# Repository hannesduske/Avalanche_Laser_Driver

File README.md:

# Nanosecond Avalanche Laser Driver

This avalanche driver generates $\mathbf{2-3\ \mathrm{ns}}$ pulses with peak pulse currents up to $\mathbf{150\ \mathrm{A}}$.
The driver integrates an adjustable boost converter to generate up to $\mathbf{320\ \mathrm{V}}$ from a low-voltage supply.

<div align="center">
<table style="border: none;">
  <tr>
    <td style="text-align:center">
      <br>
    </td>
    <td style="text-align:center">
      <br>
    </td>
  </tr>
</table>
</div>

## ⚠️ Safety Warning

**This project involves high-voltage electronics, high peak currents, and potentially hazardous laser radiation. Anyone building, modifying, or operating this design is responsible for understanding and managing these risks.**

> ⚠️ This repository contains engineering documentation and experimental hardware designs.
> It is not a certified, production-ready, or safety-tested device.

> ⚠️ The circuit contains hazardous high voltages, stored energy, and extremely high peak currents.
> Dangerous voltages may remain present even after the power source has been disconnected.

> ⚠️ Laser diodes driven by this circuit may emit optical pulses capable of causing immediate and permanent eye injury.
> Depending on the laser diode used, hazardous radiation may be invisible.

> ⚠️ Never operate this circuit without appropriate laser safety procedures, protective eyewear suitable for the wavelength used, and adequate electrical safety precautions.

<div align="center">
<table style="border: none;">
  <tr>
    <td style="text-align:center">
      <br>
    </td>
    <td style="text-align:center">
      <br>
    </td>
  </tr>
</table>

**Refer to [this explicit safety statement](SAFETY.md) for more information.**

</div>

## Table of Contents

- [1. Technical Specification](#1-technical-specification)
  - [1.1 Key Features](#11-key-features)
  - [1.2 Design Specification](#12-design-specification)
  - [1.3 Measured Performance](#13-measured-performance)
- [2. Circuit Design](#2-circuit-design)
  - [2.1 Overview](#21-overview)
  - [2.2 Input Protection](#22-input-protection)
  - [2.3 Boost Converter](#23-boost-converter)
  - [2.4 Avalanche Output Stage](#24-avalanche-output-stage)
  - [2.5 Trigger Input Stage](#25-trigger-input-stage)
- [3. PCB Layout](#3-pcb-layout)
  - [3.1 Physical Dimensions](#31-physical-dimensions)
  - [3.2 Peripheral Components](#32-peripheral-components)
  - [3.3 Assembled Driver Boards](#33-assembled-driver-boards)
- [4. Driver Performance](#4-driver-performance)
  - [4.1 Output Voltage](#41-output-voltage)
  - [4.2 Short Circuit Test](#42-short-circuit-test)
  - [4.3 Blue LED Performance](#43-blue-LED-performance)
  - [4.4 PLPT9 450LC_E Performance](#44-plpt9-450lc_e-performance)
- [5. Protective Cover](#5-protective-cover)
- [6. References](#6-references)
  - [6.1 Datasheets of Main Components](#61-datasheets-of-main-components)
  - [6.2 Reference Designs](#62-reference-designs)
  - [6.3 General Resources](#63-general-resources)
  - [6.4 Design Tools](#64-design-tools)

## 1. Technical Specification

### 1.1 Key Features

This driver circuit is built around the [FMMT417](https://www.diodes.com/datasheet/download/FMMT417.pdf) avalanche transistor and is designed to operate up to the transistor's collector-emitter voltage rating of $320\ \mathrm{V}$.
The high voltage is generated by an integrated [LT8365](https://www.analog.com/media/en/technical-documentation/data-sheets/lt8365.pdf) boost converter and can be adjusted from $160\ \mathrm{V}$ to $320\ \mathrm{V}$ to control the output pulse current.

The driver is externally triggered through a transformer-isolated $50\ \Omega$ input.
The trigger signal is internally buffered, significantly improving output pulse consistency across a wide range of trigger amplitudes and waveforms.

For monitoring the generated output pulses, the driver includes a current-sense output with a sensitivity of $100\ \mathrm{A/V}$, enabling direct observation and measurement of the output pulse waveform.

### 1.2 Design Specification

<div align="center">

| Parameter | Value |
|-|-|
| Input Voltage | $9\ \mathrm{V}$ to $30\ \mathrm{V}$ |
| Output Voltage | $160\ \mathrm{V}$ to $320\ \mathrm{V}$ |
| Output Capacitance | $200\ \mathrm{pF}$ | 
| Current Sense Output | $100\ \mathrm{A}/\mathrm{V}$ into a $50\ \Omega$ load|
| Input Protection | Reverse voltage protection <br> Short-circuit protection |
| Trigger Input | $50\ \Omega$ Input <br> Internally buffered <br> Transformer-isolated <br> Immune to DC trigger signals |

</div>

> ℹ️ The upper voltage limit is chosen to match the FMMT417's collector-emitter voltage rating of $320\ \mathrm{V}$.

> ℹ️ The actual cutoff voltage of the driver input is $7.5\ \mathrm{V}$, but it is not guaranteed that the boost converter can reach its maximum output voltage with inputs below $9\ \mathrm{V}$.

### 1.3 Measured Performance

<div align="center">

| Parameter | Value |
|-|-|
| Shortest Pulse Width | $2\ \mathrm{ns}$ |
| Maximum Pulse Current | $150\ \mathrm{A}$ |
| Minimum Avalanche Voltage | $215\ \mathrm{V}$|
| Parasitic Output Inductance | $5.5\ \mathrm{nH}$ |
| Maximum Frequency | $20\ \mathrm{kHz}$ |

</div>

> ℹ️ The maximum frequency can be increased by replacing the $47\ \mathrm{k}\Omega$ charge current-limiting resistor with a smaller one.
Read [this](#42-short-circuit-test) for details.

## 2. Circuit Design

### 2.1 Overview

<div align="center">
  <br>
</div>

The complete schematic is available [here](01_Docs/02_Schematic/avalanche_laser_driver_v0_2.pdf) as PDF.

### 2.2 Input Protection

<div align="center">
  <br>
</div>

The driver is protected against reverse input voltages through MOSFET $\mathrm{Q1}$.
Additionally, the input stage includes an SMD fuse for short-circuit protection.
A switch is added to physically turn the driver on and off.
Two green LEDs indicate whether the DC input is connected correctly and whether the switch is turned on.

### 2.3 Boost Converter

<div align="center">
  <br>
</div>

The high voltage output is generated with an LT8365 boost converter.
Two diode-capacitor stages are added to the output of the boost converter to reach the voltage rating of the FMMT417.
The two additional stages reduce the current available for charging the output capacitors and the output charging resistor $\mathrm{R12}$ is sized accordingly.

The output voltage is set by the feedback network formed by $\mathrm{R5}$, $\mathrm{R7}$ and $\mathrm{RV1}$.
The ratio of $\mathrm{R5}$ to $\mathrm{R7}$ sets the maximum output voltage $\mathrm{HV\_OUT}$ and $\mathrm{R7}$ is tuned to achieve a $320\ \mathrm{V}$ output with the assembled circuit.
The theoretical maximum voltage with the selected values $\mathrm{R5}=1\ \mathrm{M}\Omega$ and $\mathrm{R7}=4.81\ \mathrm{k}\Omega$ is $334\ \mathrm{V}$.

The potentiometer $\mathrm{RV1}$ sets the adjustment range of the output voltage.
It should cover the entire range from the FMMT417's minimum avalanche voltage (around $215\ \mathrm{V}$) to its collector-emitter voltage rating of $320\ \mathrm{V}$.
The chosen value of $5\ \mathrm{k}\Omega$ is larger than necessary for that purpose, as it gives a lower voltage limit of $160\ \mathrm{V}$.
Using a smaller value potentiometer (around $3.3\ \mathrm{k}\Omega$) would enable finer adjustments while still covering the entire voltage range.

The third terminal of $\mathrm{RV1}$ is also connected so that, if the potentiometer wiper fails open-circuit, the potentiometer defaults to its maximum resistance.
In that case the boost converter falls back to its minimum output voltage.

A red LED indicates whether the boost converter output capacitors are charged.

### 2.4 Avalanche Output Stage

<div align="center">
  <br>
</div>

The core of this driver is a basic avalanche transistor circuit.
The high voltage output capacitors $\mathrm{C11}$ and $\mathrm{C12}$ are charged through the current-limiting resistor $\mathrm{R12}$ and the charging diode $\mathrm{D9}$.
Once charged, a small signal at the base of the transistor $\mathrm{Q2}$ initiates avalanche breakdown across the collector-emitter junction, resulting in the rapid discharge of $\mathrm{C11}$ and $\mathrm{C12}$ through the output load.
After an output pulse the capacitors recharge again.

One goal of the output stage is to minimize the parasitic inductance as it is the main limiting factor for the peak pulse current during fast transients.
Therefore, multiple smaller output capacitors in parallel are preferred over a single large one because the effective equivalent series inductance (ESL) is reduced.
In this design two $100\ \mathrm{pF}$ 0603 capacitors are used, as the only other smaller capacitors with sufficient current rating ($47\ \mathrm{pF}$) were not in stock at the time the driver boards were assembled.

The components $\mathrm{C11}$, $\mathrm{C12}$ and $\mathrm{R12}$ form an RC low-pass which sets the maximum frequency at which the circuit can be triggered.
Assuming that approximately three time constants are required for capacitor recharge, the maximum frequency is approximately $f_{max}\approx \frac{1}{3\cdot \mathrm{R_{12}}(\mathrm{C_{11}}+\mathrm{C_{12}})} = \frac{1}{3 \cdot 47\ \mathrm{k}\Omega(100\ \mathrm{pF}+100\ \mathrm{pF})} \approx 35\ \mathrm{kHz}$.
The actual frequency is lower than that because the capacitors do not start charging immediately after a pulse, as is shown by the measurements below.

In this design the driver capacitance is $200\ \mathrm{pF}$ with a maximum output voltage of $320\ \mathrm{V}$.
The maximum stored electrical energy per pulse is $E_p=\frac{1}{2}\cdot C \cdot U^2=\frac{1}{2}\cdot 200\ \mathrm{pF} \cdot (320\ \mathrm{V})^2=10.24\ \mu\mathrm{J}$.
With the maximum achievable trigger frequency of $20\ \mathrm{kHz}$ (see measurements below) the maximum theoretical average output power is approximately $P=E_p\cdot f=10.24\ \mu\mathrm{J}\cdot 20\ \mathrm{kHz}=205\ \mathrm{mW}$

The $20\ \mathrm{m}\Omega$ four-terminal shunt resistor $\mathrm{R19}$ is placed in series with the driver output, enabling the pulse current to be monitored.
This low-value resistor has a minimal effect on the pulse current while providing accurate measurements through its two sense terminals.
The circuit's sense output is designed to drive a $50\ \Omega$-terminated oscilloscope input.
Together with the external $50\ \Omega$ termination resistor, the internal $50\ \Omega$ resistor $\mathrm{R15}$ forms a $1:2$ voltage divider.
The $20\ \mathrm{m}\Omega$ shunt resistor provides a sensitivity of $20\ \mathrm{mV/A}$.
This is halved by the voltage divider, resulting in a final sensitivity of $10\ \mathrm{mV/A}$ or $100\ \mathrm{A/V}$ at the circuit's current sense output.

### 2.5 Trigger Input Stage

<div align="center">
  <br>
</div>

The trigger input feeds a $50\ \Omega$ terminated balun transformer $\mathrm{TR1}$ for isolation and for high-pass filtering of the input.
The transformed signal is then buffered by the high-speed BJT $\mathrm{Q3}$ which is connected to the FMMT417's base through the current-limiting resistor $\mathrm{R14}$.
The pull-down resistor $\mathrm{R21}$ helps turn off $\mathrm{Q2}$ rapidly after an avalanche and prevents accidental triggering caused by a floating base.

The high-pass property of the balun transformer also prevents damage to $\mathrm{Q2}$ from DC input signals which would otherwise keep the avalanche transistor turned on.

## 3. PCB Layout

### 3.1 Physical Dimensions

Below is an illustration of the physical outline and hole spacing of the PCB V0.2.
The mounting holes fit the standard $25\ \mathrm{mm}$ hole pattern of optical benches.

<div align="center">
  <br>
</div>

### 3.2 Peripheral Components

Below is a functional description of the main peripheral components of the PCB.

<div align="center">
<br>

| Reference | Description |
|-|-|
| SW1   | On/off switch. Switches the supply rail of the boost converter. |
| POT1  | Output voltage adjustment. |
| LED1  | Indicates DC input is connected. |
| LED2  | Indicates the boost converter is supplied. Lights up when SW1 is on. |
| LED3  | Indicates the boost converter output caps are charged. | 
| SMA1  | Trigger input ($50\ \Omega$). | 
| SMA2  | Current sense output ($50\ \Omega$). |
| CONN1 | DC input. 5.5 x 2.1 mm barrel jack (center positive). |
| CONN2 | Driver output. Solder pads ($2\ \mathrm{mm}$ pitch). |
| FUSE1 | 0603 SMD Fuse ($3\ \mathrm{A}$) for short-circuit protection. |
</div>

### 3.3 Assembled Driver Boards

The two driver boards shown below were assembled for a performance test.
The left driver was assembled with an ams OSRAM PLPT9 450LC_E laser diode and the right one with a blue LED.

<div align="center">
<table style="border: none;">
  <tr>
    <td style="text-align:center">
      <br>
      <p>Top view of the V0.2 PCBs</p>
    </td>
    <td style="text-align:center">
        <br>
      <p>Front view of the V0.2 PCBs</p>
    </td>
  </tr>
</table>
</div>

## 4. Driver Performance

Driver performance was evaluated using the following configurations:
- Output pads shorted with solder bridge
- Blue LED (right PCB in above pictures)
- ams OSRAM PLPT9 450LC_E (left PCB in above pictures)

### 4.1 Output Voltage

The output voltage of the driver is adjustable between $160\ \mathrm{V}$ and $320\ \mathrm{V}$.

<div align="center">
<table style="border: none;">
  <tr>
    <td style="text-align:center">
      <br>
      <p>Lower voltage limit of the boost converter</p>
    </td>
    <td style="text-align:center">
        <br>
      <p>Upper voltage limit of the boost converter</p>
    </td>
  </tr>
</table>
</div>

> ⚠️ The feedback resistors should not be replaced to increase the upper voltage limit above $320\ \mathrm{V}$.
> Increasing the output voltage risks instant destruction of the FMMT417.

### 4.2 Short-Circuit Test

In the first test the output pads of the driver are shorted with a solder bridge.
The output is set to $320\ \mathrm{V}$ and the trigger signal is a $2\ \mathrm{Vpp}$ square wave.

<div align="center">
  <br>
  <p>Short-circuit test at 320 V with a 2 Vpp trigger signal</p>
</div>

The short-circuit test shows that the output oscillates with no load connected.
This is the expected behavior, because the stored energy is dissipated only slowly through the parasitic impedance of the circuit and there is no diode that blocks reverse current.

In the short-circuit test we measured a maximum current of $153\ \mathrm{A}$ with a pulse width of $2.2\ \mathrm{ns}$.

The minimum operating voltage at which avalanche triggering occurs was measured to be 215 V with a 5 V square wave trigger signal.
Note that the minimum voltage depends on the trigger signal amplitude.
The lower the output voltage, the larger the trigger signal amplitude must be to start an avalanche.

We can also approximate the effective parasitic loop inductance of the output stage from the observed oscillation.
For this, we assume an LC oscillator with a frequency of $f = \frac{1}{2 \pi \sqrt{LC}}$.
From the measured oscillation frequency we get $f = 152\ \mathrm{MHz}$ and the output capacitance is $200\ \mathrm{pF}$.
With these values we calculate an inductance of $L = \frac{1}{C(2\pi f)^2} = \frac{1}{200\ \mathrm{pF}(2\pi \cdot 152\ \mathrm{MHz})^2} = 5.46\ \mathrm{nH}$.

<div align="center">
  <br>
  <p>Measurement of the output capacitor charge time</p>
</div>

In a second measurement the maximum trigger frequency is tested.
The measurement shows that the output capacitors start charging only after a delay of $14\ \mathrm{\mu s}$.
This reduces the actual achievable output frequency from the theoretical $35\ \mathrm{kHz}$ to a practically achievable frequency of $20\ \mathrm{kHz}$.

### 4.3 Blue LED Performance

In the second test the output drives a blue LED.
The output is set to $320\ \mathrm{V}$ and the trigger signal is a $2\ \mathrm{Vpp}$ square wave.

<div align="center">
  <br>
  <p>Test with blue LED at 320 V with a 2 Vpp trigger signal</p>
</div>

With the blue LED, the output pulse is significantly different compared to the short-circuit test.
There is a large, narrow current pulse across the diode, followed by a smaller, wider pulse in the reverse direction.
With the blue LED, the maximum current is $70\ \mathrm{A}$ with a $2\ \mathrm{ns}$ pulse width.

In a second test, the optical pulse shape was measured at a lower drive current with the [Fast SiPM Photodetector](https://github.com/hannesduske/Fast_SiPM_Photodetector).
The cyan trace shows the drive-current pulse, and the yellow trace shows the measured SiPM response to the LED's light emission.
The oscilloscope measured pulse widths of $2.35\ \mathrm{ns}$ for the drive-current pulse and $5.55\ \mathrm{ns}$ for the SiPM output.
The SiPM output pulse is significantly wider than the drive-current pulse.

<div align="center">
  <br>
  <p>Drive-current pulse (cyan) through the blue LED and the measured SiPM output (yellow) averaged over 64 measurements.</p>
</div>

### 4.4 PLPT9 450LC_E Performance

In the third test the output drives an ams OSRAM PLPT9 450LC_E.
The output is set to $320\ \mathrm{V}$ and the trigger signal is a $2\ \mathrm{Vpp}$ square wave.

<div align="center">
  <br>
  <p>Test with PLPT9 450LC_E at 320 V with a 2 Vpp trigger signal</p>
</div>

With the PLPT9 laser diode the maximum current is $141\ \mathrm{A}$ with a $2\ \mathrm{ns}$ pulse width.

Note that the oscillation is less damped than with the blue LED and more similar to the short-circuit test.
Presumably this is because of the integrated reverse-protection Zener diode in the PLPT9 package, which protects the sensitive main laser diode against reverse currents.

The optical pulse shape was measured with the [Fast SiPM Photodetector](https://github.com/hannesduske/Fast_SiPM_Photodetector).
The oscillations in the drive-current pulse are also visible as additional peaks in the measured SiPM response, showing that they carry through to the laser's light emission.
Similar to the short-circuit test, the oscillation frequency is approximately 150 MHz.

<div align="center">
  <br>
  <p>Drive-current pulse (cyan) through the PLPT9 450LC_E laser diode and the measured SiPM output (yellow) averaged over 64 measurements.</p>
</div>

## 5. Protective Cover

A 3D printed cover has been designed for the driver.
It covers the high voltage components and exposes only the peripherals.

The cover is available in two variants.
A monolithic version that is easy to print and a version with **T**rigger/ **S**ense markings for printers with filament change capability.

<div align="center">
<table style="border: none;">
  <tr>
    <td style="text-align:center">
      <br>
      <p>Monolithic cover</p>
    </td>
    <td style="text-align:center">
      <br>
      <p>Cover with Trigger/ Sense markings</p>
    </td>
  </tr>
</table>
</div>

## 6. References
### 6.1 Datasheets of Main Components
- [LT8365](https://www.analog.com/media/en/technical-documentation/data-sheets/lt8365.pdf) Boost converter
- [FMMT417](https://www.diodes.com/datasheet/download/FMMT417.pdf) Avalanche transistor
- [PLPT9 450LC_E](https://look.ams-osram.com/m/8992eec443b4ce2/original/PLPT9-450LC_E.pdf) ams OSRAM Laser Diode

### 6.2 Reference Designs
- [Les' Lab Laser Driver](https://github.com/leswright1977/avalanche-laser-diode-driver) + [Video](https://www.youtube.com/watch?v=3-htF8Jrixo&t=24s) (ZTX415/ 2N5192G)
- [BigPulse Driver](https://github.com/MazinLab/BigPulse) + [Video](https://www.youtube.com/watch?v=OXhiX0EW5MI) (FMMT415TD + LT8365)

### 6.3 General Resources
- Lasercomponents [Whitepaper](https://www.lasercomponents.com/uk/photonics-portal/knowledge-center/whitepapers/drive-electronics-for-pulsed-laser-diodes/)
- Zetex ZTX415 [Application Note AN8](https://user-web.icecube.wisc.edu/~kitamura/NK/Flasher_Board/Useful/research/AN8.pdf)
- Jim Williams Pulser [AN47 Appendix D (p. 93)](https://www.analog.com/media/en/technical-documentation/application-notes/an47fa.pdf)
- Selection and usage of laser safety goggles [DGUV 203-042](https://publikationen.dguv.de/widgets/pdf/download/article/249) (German)
- Continuous wave laser diodes enable fast optoacoustic imaging [ResearchGate](https://www.researchgate.net/publication/321863583_Continuous_wave_laser_diodes_enable_fast_optoacoustic_imaging)

### 6.4 Design Tools
- [LTSpice](https://www.analog.com/en/resources/design-tools-and-calculators/ltspice-simulator.html) Circuit simulation
- [KiCad 10](https://www.kicad.org/blog/2026/03/Version-10.0.0-Released/) Circuit board design
- [SMath Studio](https://smath.com/) Design calculations

## License

This project is licensed under the CERN Open Hardware Licence Version 2 - Permissive ([CERN-OHL-P](https://ohwr.org/cern_ohl_p_v2.txt)).

Third-party datasheets, logos, warning symbols, and referenced documentation remain the property of their respective owners.

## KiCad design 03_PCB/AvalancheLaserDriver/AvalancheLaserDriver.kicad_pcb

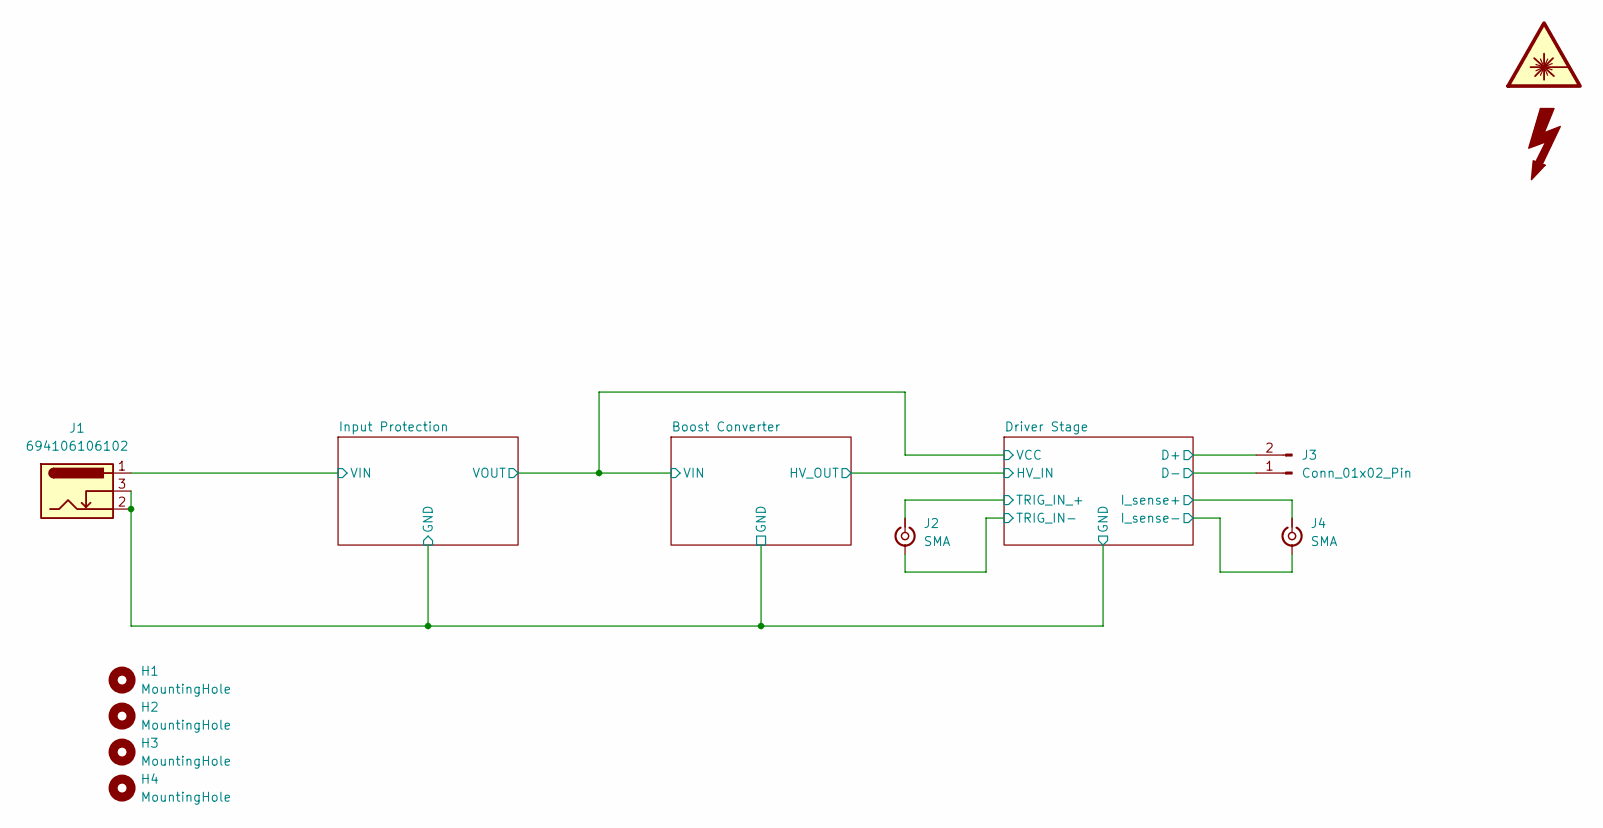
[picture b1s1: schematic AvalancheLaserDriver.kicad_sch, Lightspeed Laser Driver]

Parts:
H1, H2, H3, H4: MountingHole; MountingHole_3.2mm_M3
J1: 694106106102; BarrelJack_Wuerth_694106106102_2.0x5.5mm
J2, J4: SMA; SMA_Wurth_60312002114503_Vertical
J3: Conn_01x02_Pin; R_0815_2038Metric_Pad1.20x4.05mm_HandSolder

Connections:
/Driver Stage/D+: J3.2; also elsewhere on the board
/Driver Stage/D-: J3.1; also elsewhere on the board
/Driver Stage/I_sense+: J4.1 (In); also elsewhere on the board
/Driver Stage/I_sense-: J4.2 (Ext); also elsewhere on the board
/Driver Stage/TRIG_IN-: J2.2 (Ext); also elsewhere on the board
/Driver Stage/TRIG_IN_+: J2.1 (In); also elsewhere on the board
/Input Protection/VIN: J1.1; also elsewhere on the board
GND: J1.2, J1.3; also elsewhere on the board

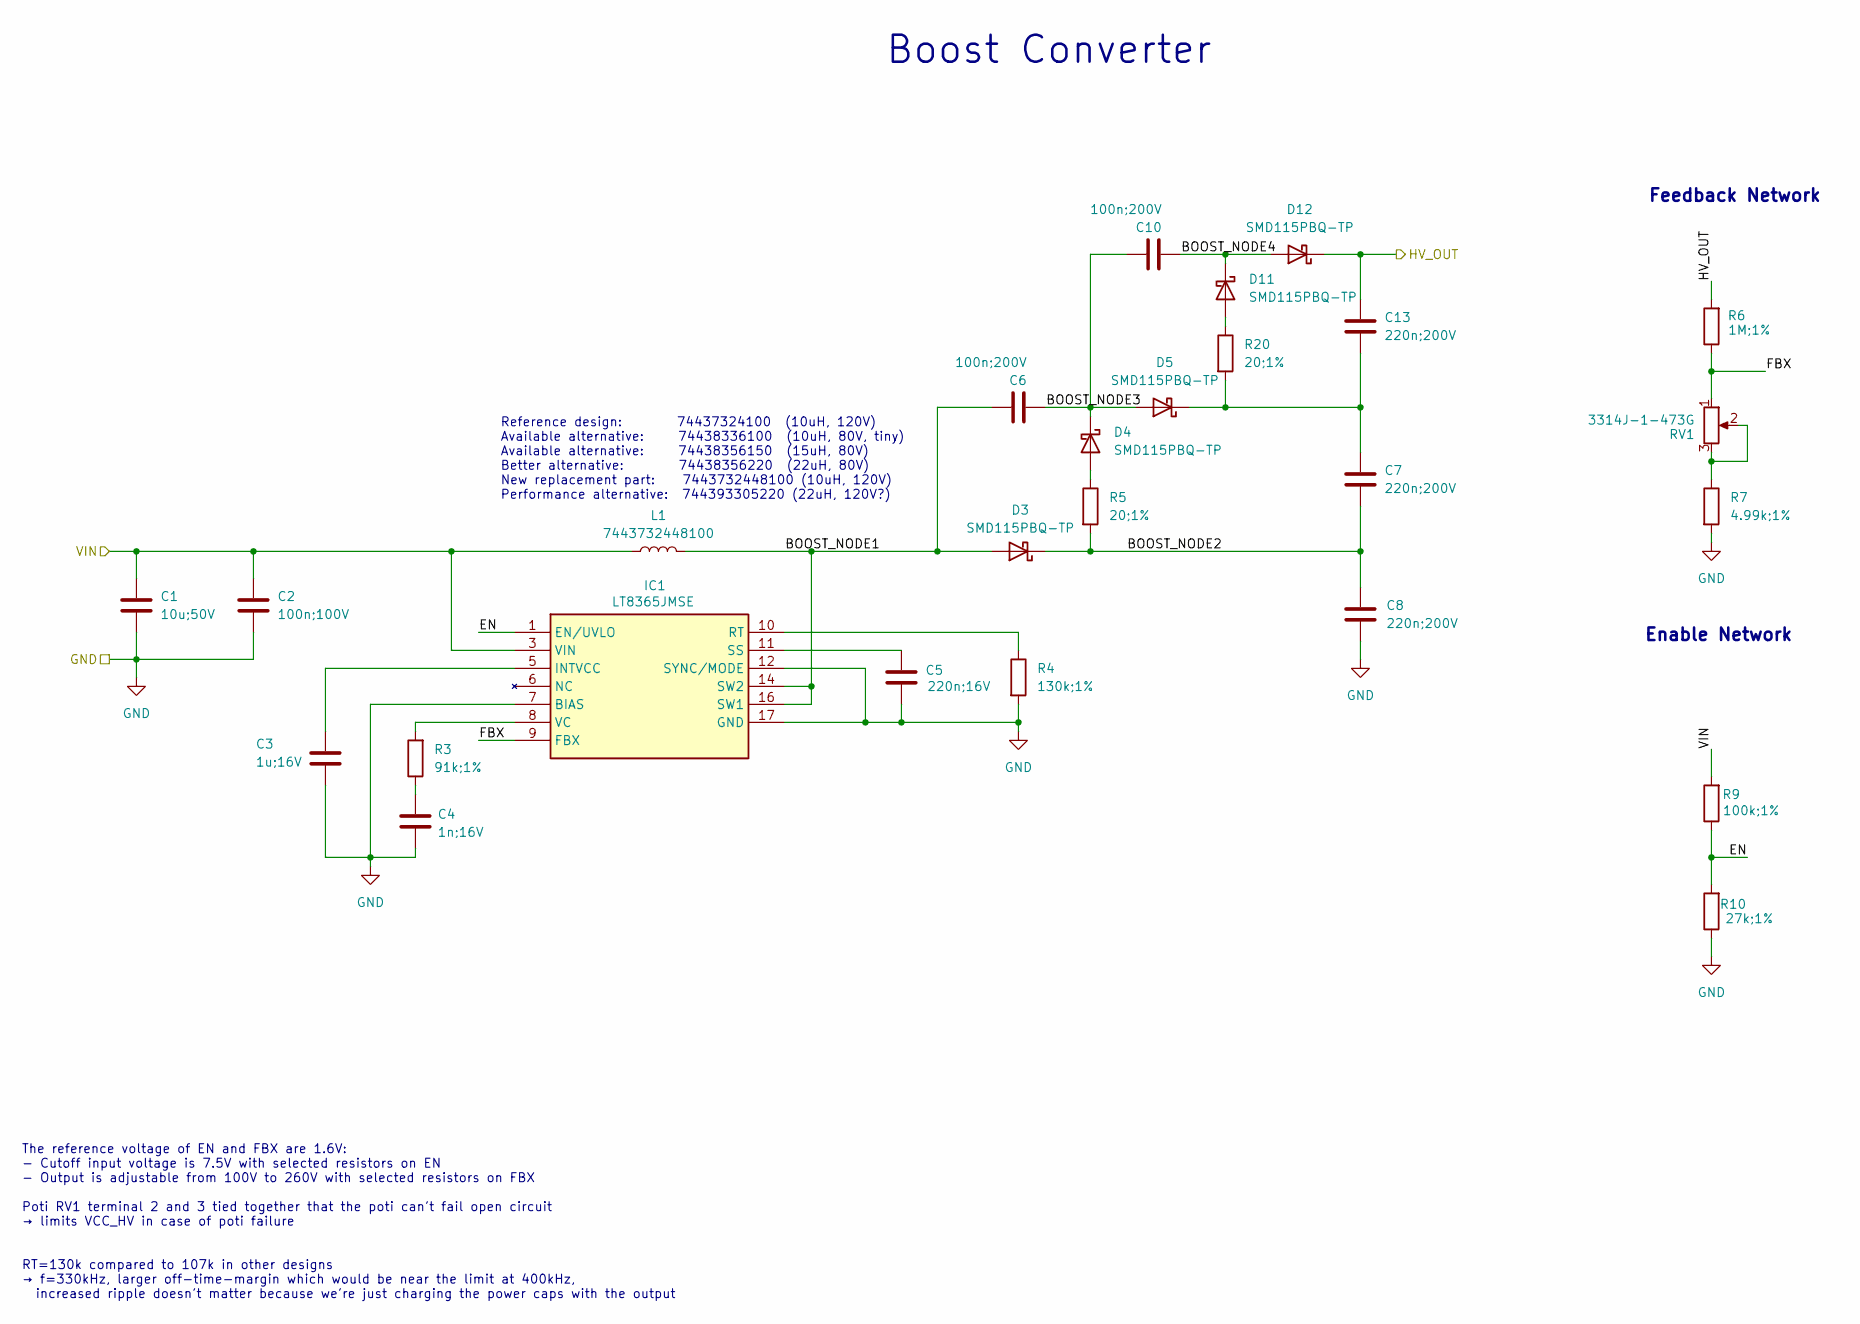
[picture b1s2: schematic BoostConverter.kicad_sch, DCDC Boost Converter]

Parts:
C1: 10u;50V; C_1206_3216Metric
C2: 100n;100V; C_0603_1608Metric
C3: 1u;16V; C_0603_1608Metric
C4: 1n;16V; C_0603_1608Metric
C5: 220n;16V; C_0603_1608Metric
C6, C10: 100n;200V; C_0805_2012Metric
C7, C8, C13: 220n;200V; C_1206_3216Metric
D3, D4, D5, D11, D12: SMD115PBQ-TP; D_SOD-323HE
IC1: LT8365JMSE; Analog_MSOP-12-16-1EP_3x4.039mm_P0.5mm_EP1.651x2.845mm; Mouser Part Number 584-LT8365JMSE
L1: 7443732448100; L_Wurth_WE-LQSH-4020
R3: 91k;1%; R_0603_1608Metric
R4: 130k;1%; R_0603_1608Metric
R5, R20: 20;1%; R_0603_1608Metric
R6: 1M;1%; R_0603_1608Metric
R7: 4.99k;1%; R_0603_1608Metric
R9: 100k;1%; R_0603_1608Metric
R10: 27k;1%; R_0603_1608Metric
RV1: 3314J-1-473G; Potentiometer_Bourns_3314J_Vertical

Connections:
/Boost Converter/BOOST_NODE1: C6.1, D3.2 (A), IC1.14 (SW2), IC1.16 (SW1), L1.2
/Boost Converter/BOOST_NODE2: C7.1, C8.2, D3.1 (K), R5.2
/Boost Converter/BOOST_NODE3: C6.2, C10.1, D4.1 (K), D5.2 (A)
/Boost Converter/BOOST_NODE4: C10.2, D11.1 (K), D12.2 (A)
/Boost Converter/EN: IC1.1 (EN/UVLO), R9.1, R10.2
/Boost Converter/FBX: IC1.9 (FBX), R6.1, RV1.1
/Boost Converter/HV_OUT: C13.2, D12.1 (K), R6.2; also elsewhere on the board
/Boost Converter/VIN: C1.2, C2.2, IC1.3 (VIN), L1.1, R9.2; also elsewhere on the board
GND: C1.1, C2.1, C3.1, C4.1, C5.1, C8.1, IC1.7 (BIAS), IC1.12 (SYNC/MODE), IC1.17 (GND), R4.2, R7.2, R10.1; also elsewhere on the board
unnamed: C4.2, R3.1
unnamed: D4.2 (A), R5.1
unnamed: C7.2, C13.1, D5.1 (K), R20.2
unnamed: D11.2 (A), R20.1
unnamed: C3.2, IC1.5 (INTVCC)
unnamed: IC1.10 (RT), R4.1
unnamed: C5.2, IC1.11 (SS)
unnamed: IC1.8 (VC), R3.2
unnamed: R7.1, RV1.2, RV1.3

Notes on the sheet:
Enable Network
The reference voltage of EN and FBX are 1.6V: - Cutoff input voltage is 7.5V with selected resistors on EN - Output is adjustable from 100V to 260V with selected resistors on FBX Poti RV1 terminal 2 and 3 tied together that the poti can't fail open circuit → limits VCC_HV in case of poti failure RT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
Reference design: 74437324100 (10uH, 120V) Available alternative: 74438336100 (10uH, 80V, tiny) Available alternative: 74438356150 (15uH, 80V) Better alternative: 74438356220 (22uH, 80V) New replacement part: 7443732448100 (10uH, 120V) Performance alternative: 744393305220 (22uH, 120V?)
Boost Converter
Feedback Network

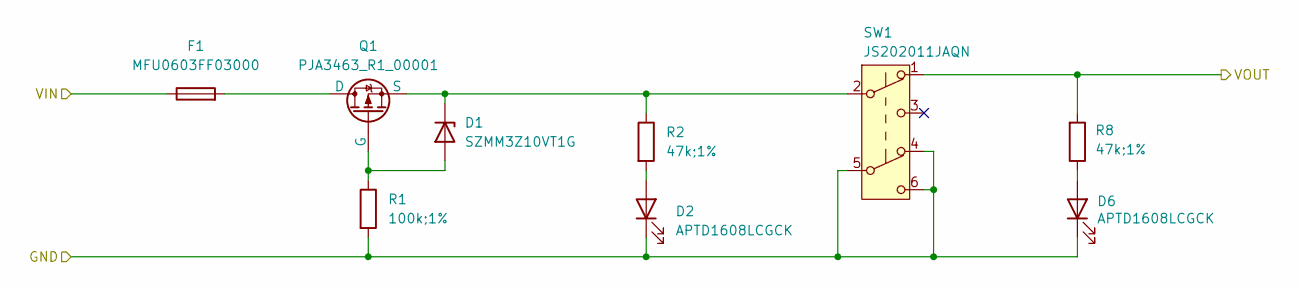
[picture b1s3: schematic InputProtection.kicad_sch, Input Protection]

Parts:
D1: SZMM3Z10VT1G; D_SOD-323
D2, D6: APTD1608LCGCK; LED_0603_1608Metric
F1: MFU0603FF03000; Fuse_0603_1608Metric
Q1: PJA3463_R1_00001; SOT-23
R1: 100k;1%; R_0603_1608Metric
R2, R8: 47k;1%; R_0603_1608Metric
SW1: JS202011JAQN; SW_DPDT_CK_JS202011JCQN

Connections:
/Boost Converter/VIN: R8.2, SW1.1 (A); also elsewhere on the board
/Input Protection/VIN: F1.1; also elsewhere on the board
GND: D2.1 (K), D6.1 (K), R1.2, SW1.4 (A), SW1.5 (B), SW1.6 (C); also elsewhere on the board
unnamed: D1.2 (A), Q1.1 (G), R1.1
unnamed: D1.1 (K), Q1.2 (S), R2.1, SW1.2 (B)
unnamed: D2.2 (A), R2.2
unnamed: D6.2 (A), R8.1
unnamed: F1.2, Q1.3 (D)

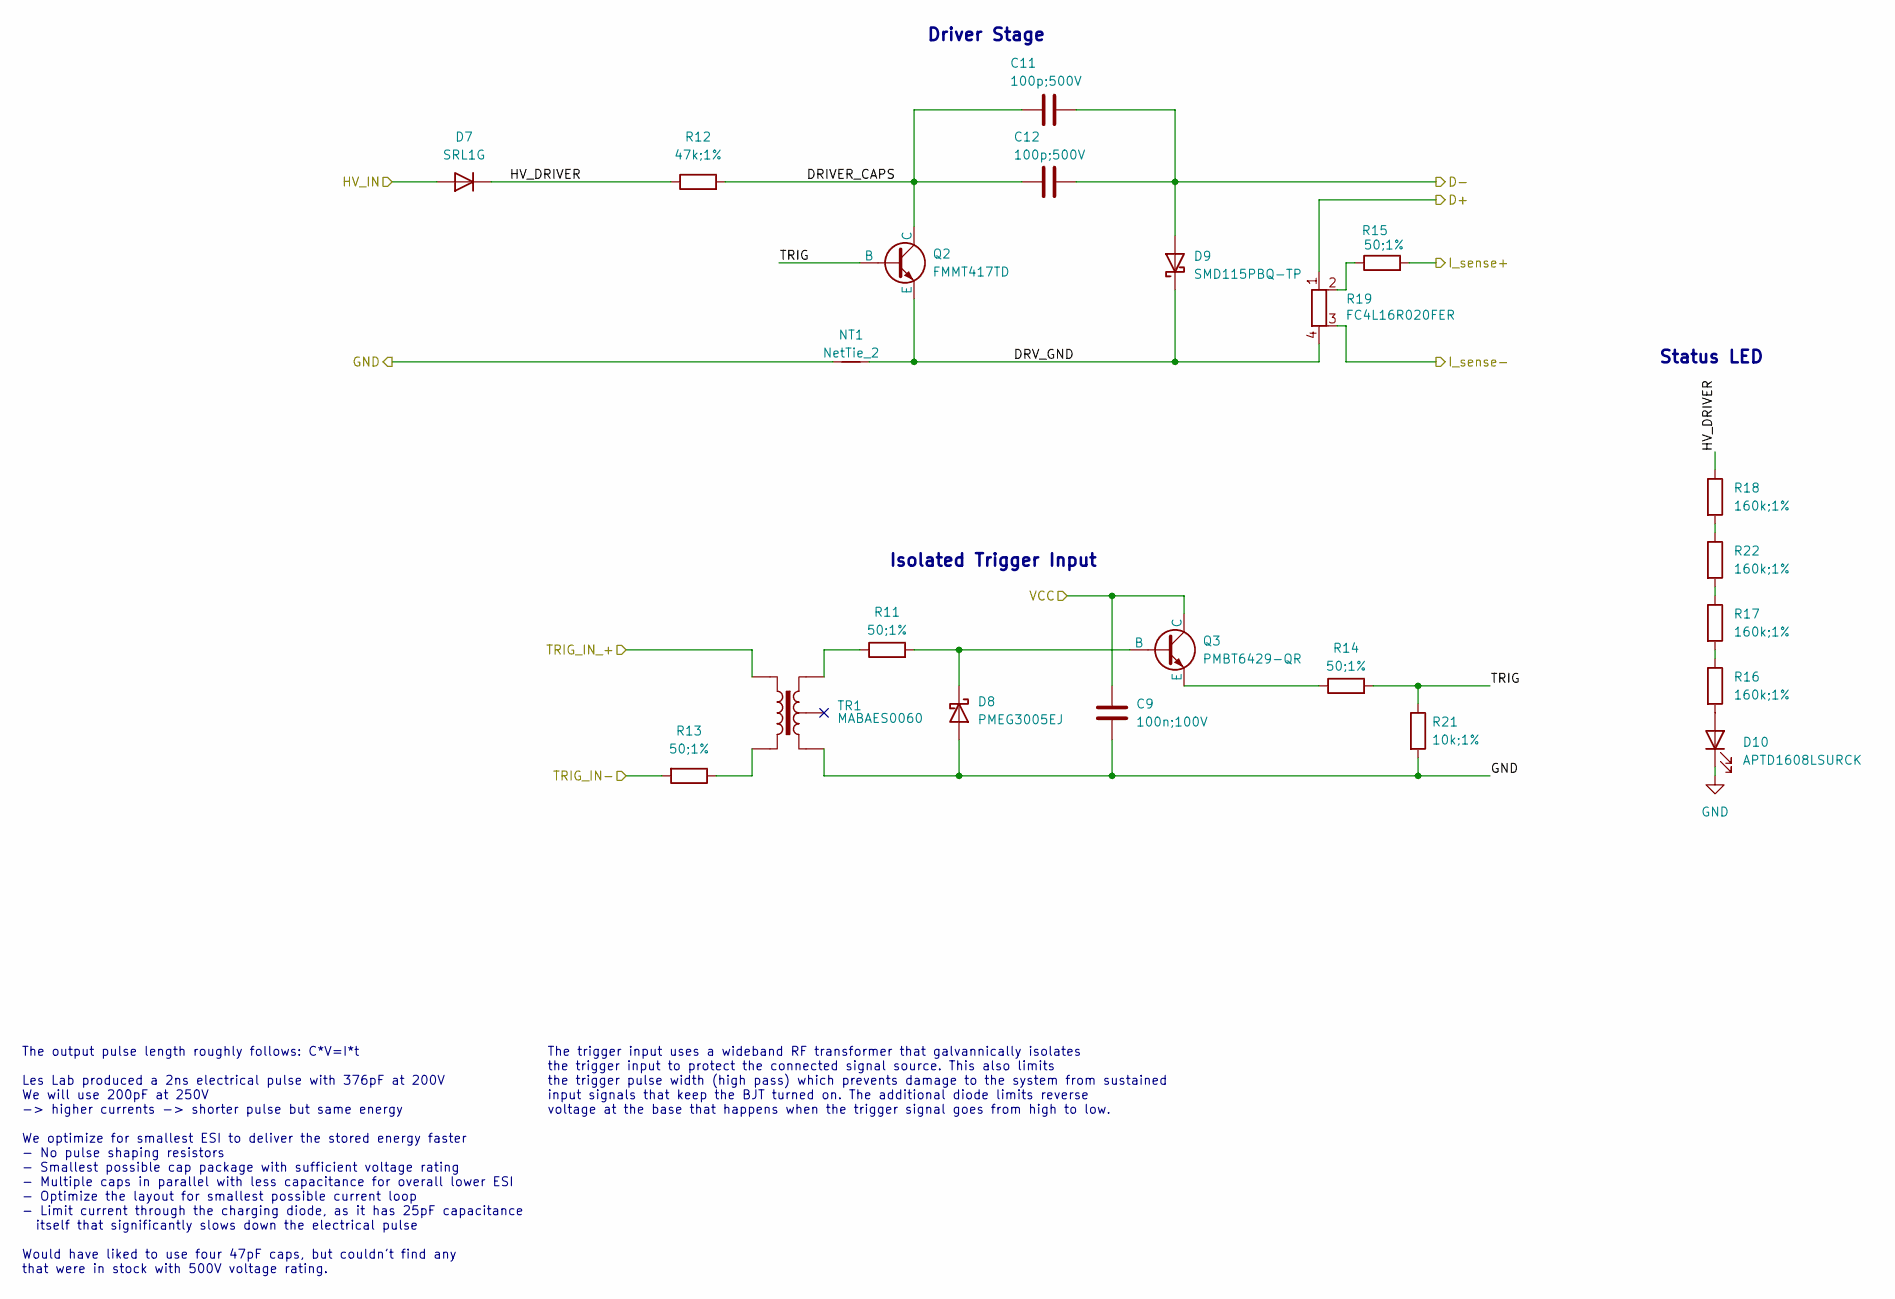
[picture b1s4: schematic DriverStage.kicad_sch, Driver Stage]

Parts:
C9: 100n;100V; C_0603_1608Metric
C11, C12: 100p;500V; C_0603_1608Metric
D7: SRL1G; D_SOD-323HE
D8: PMEG3005EJ; D_SOD-323
D9: SMD115PBQ-TP; D_SOD-323HE
D10: APTD1608LSURCK; LED_0603_1608Metric
NT1: NetTie_2; NetTie-2_THT_Pad0.3mm
Q2: FMMT417TD; TSOT-23
Q3: PMBT6429-QR; TSOT-23
R11, R13, R14, R15: 50;1%; R_0603_1608Metric
R12: 47k;1%; R_0603_1608Metric
R16, R17, R18, R22: 160k;1%; R_0603_1608Metric
R19: FC4L16R020FER; FC4L16
R21: 10k;1%; R_0603_1608Metric
TR1: MABAES0060; Transformer_MACOM_SM-22

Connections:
/Boost Converter/HV_OUT: D7.2 (A); also elsewhere on the board
/Boost Converter/VIN: C9.2, Q3.3 (C); also elsewhere on the board
/Driver Stage/D+: R19.1; also elsewhere on the board
/Driver Stage/D-: C11.2, C12.2, D9.2 (A); also elsewhere on the board
/Driver Stage/DRIVER_CAPS: C11.1, C12.1, Q2.3 (C), R12.2
/Driver Stage/DRV_GND: D9.1 (K), NT1.2, Q2.2 (E), R19.4
/Driver Stage/HV_DRIVER: D7.1 (K), R12.1, R18.1
/Driver Stage/I_sense+: R15.2; also elsewhere on the board
/Driver Stage/I_sense-: R19.3; also elsewhere on the board
/Driver Stage/TRIG: Q2.1 (B), R14.2, R21.1
/Driver Stage/TRIG_IN-: R13.2; also elsewhere on the board
/Driver Stage/TRIG_IN_+: TR1.2; also elsewhere on the board
GND: C9.1, D8.2 (A), D10.1 (K), NT1.1, R21.2, TR1.5; also elsewhere on the board
unnamed: D8.1 (K), Q3.1 (B), R11.2
unnamed: D10.2 (A), R16.2
unnamed: Q3.2 (E), R14.1
unnamed: R11.1, TR1.3
unnamed: R13.1, TR1.1
unnamed: R15.1, R19.2
unnamed: R16.1, R17.2
unnamed: R17.1, R22.2
unnamed: R18.2, R22.1

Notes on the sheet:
The trigger input uses a wideband RF transformer that galvannically isolates the trigger input to protect the connected signal source. This also limits the trigger pulse width (high pass) which prevents damage to the system from sustained input signals that keep the BJT turned on. The additional di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
Isolated Trigger Input
Status LED
The output pulse length roughly follows: C*V=I*t Les Lab produced a 2ns electrical pulse with 376pF at 200V We will use 200pF at 250V -> higher currents -> shorter pulse but same energy We optimize for smallest ESI to deliver the stored energy faster - No pulse shaping resistors - Smallest possible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
Driver Stage

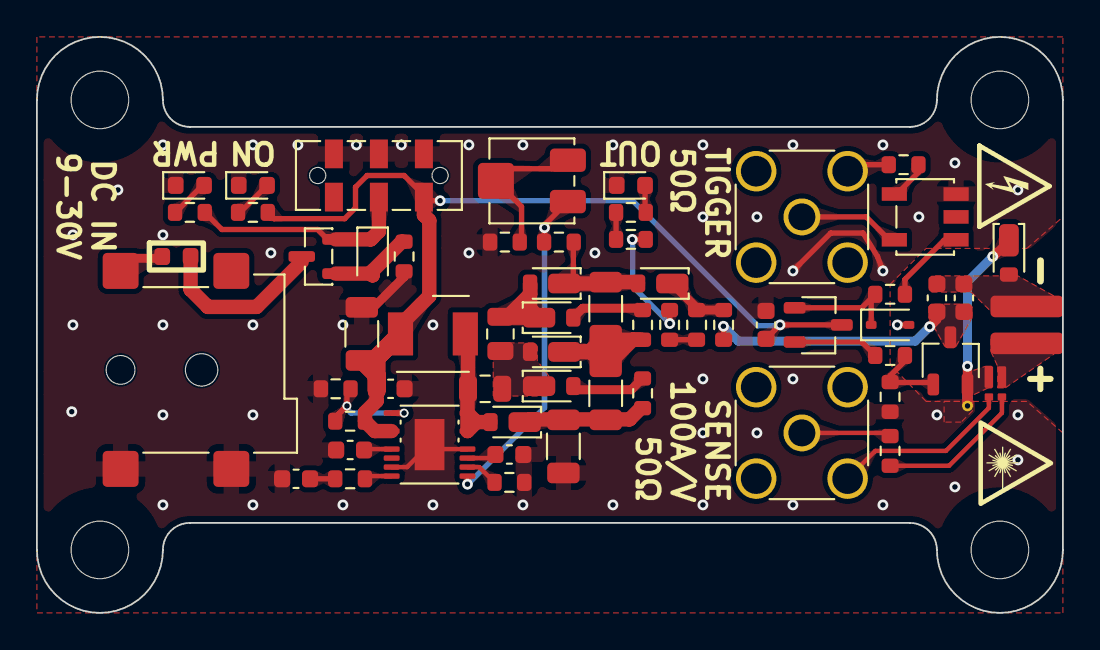
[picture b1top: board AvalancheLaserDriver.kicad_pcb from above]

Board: 2 copper layers, 57.0 x 32.0 mm, 65 parts (0 on the bottom side), 43 nets.

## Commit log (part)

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2026-06-22 feat(pcb): intital pcb layout
2026-06-22 feat(simulation): add a lt8365 simulation including the led driver stage
2026-06-22 feat(pcb): add peripherals to PCB
2026-06-22 feat(pcb): route all traces
2026-06-22 feat(pcb): laser driver layout draft finished, add high voltage indicator LED and discharge path
2026-06-22 feat(pcb): improve the design draft
2026-06-22 feat(pcb): laser driver V0.1 as ordered on 08.03.2026
2026-06-22 chore: restructure desing files in repo
2026-06-22 feat(pcb): add changelog
2026-06-22 refactor(pcb): rename laser driver PCB to AvalancheLaserDriver
2026-06-22 feat(pcb): edit component values after assembling first prototype
2026-06-22 feat(pcb): update laser driver circuit after first iteration
2026-06-22 feat(pcb): Increase operating voltage to 320V
2026-06-22 feat(pcb): finalize layout of PCB V0.2
2026-06-22 feat(pcb): laser driver V0.2 as ordered on 08.04.2026
2026-06-22 feat(pcb): add assembly files for V0.2
2026-06-22 chore(pcb): update schematic with tuned component values and update notes
2026-06-22 docs(pcb): update changelog
2026-06-22 chore: move images
2026-06-22 feat: update design files
2026-06-26 chore: add CERN-OHL-P license
2026-06-26 docs: add SAFETY.md
2026-06-26 chore: add .gitignore
2026-06-26 docs: document this project
2026-06-27 docs: document current sense output
